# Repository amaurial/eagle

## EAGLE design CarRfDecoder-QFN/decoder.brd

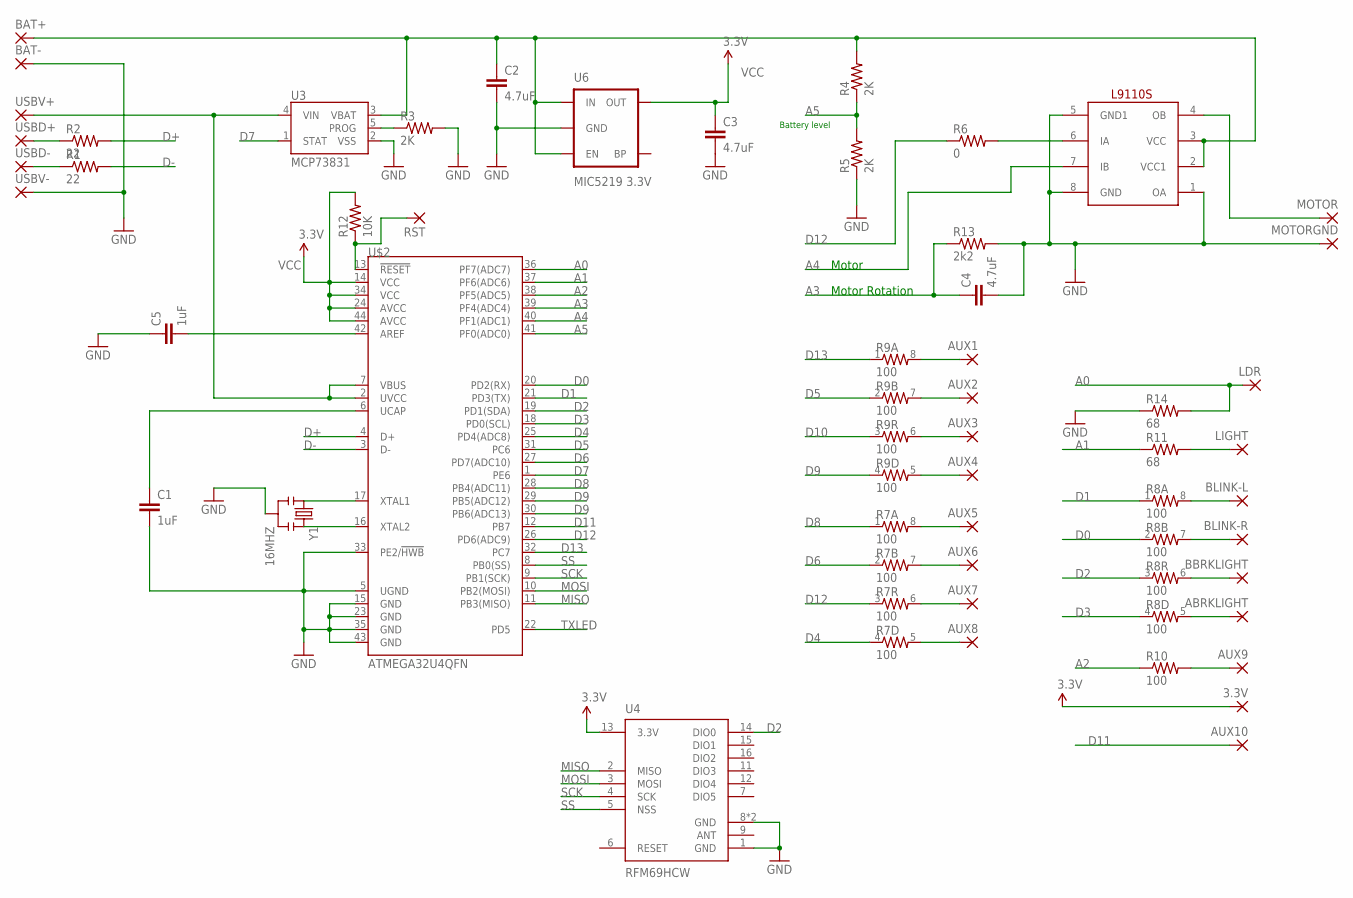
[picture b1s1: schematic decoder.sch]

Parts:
3.3V: SMD2; SMD1,27-2,54
ABRKLIGHT: SMD2; SMD1,27-2,54
AUX1, AUX2, AUX3, AUX4, AUX5, AUX6, AUX7, AUX8, AUX9, AUX10: SMD2; SMD1,27-2,54
BAT+: SMD2; SMD1,27-2,54
BAT-: SMD2; SMD1,27-2,54
BBRKLIGHT: SMD2; SMD1,27-2,54
BLINK-L: SMD2; SMD1,27-2,54
BLINK-R: SMD2; SMD1,27-2,54
C1, C5: 1uF; 0805
C2, C3, C4: 4.7uF; 0805
LDR: SMD2; SMD1,27-2,54
LIGHT: SMD2; SMD1,27-2,54
MOTOR: SMD2; SMD1,27-2,54
MOTORGND: SMD2; SMD1,27-2,54
R1, R2: 22; 0603-RES
R3, R4, R5: 2K; 0603-RES
R6: 0; 0603-RES
R7, R8, R9: 100; 0603-ARV
R10: 100; 0603-RES
R11, R14: 68; 0603-RES
R12: 10K; 0603-RES
R13: 2k2; 0603-RES
RST: SMD2; SMD1,27-2,54
U3: MCP73831; SOT23-5
U4: RFM69HCW; RFM69HCW-XXXS2
U6: MIC5219 3.3V; SOT23-5
U$1: L9110S; SO08
U$2: ATMEGA32U4QFN; SPARKFUN-DIGITALIC_QFN-44
USBD+: SMD2; SMD1,27-2,54
USBD-: SMD2; SMD1,27-2,54
USBV+: SMD2; SMD1,27-2,54
USBV-: SMD2; SMD1,27-2,54
Y1: 16MHZ; RESONATOR-SMD

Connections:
A0: LDR.1, R14.2, U$2.36 (PF7(ADC7))
A1: R11.1, U$2.37 (PF6(ADC6))
A2: R10.1, U$2.38 (PF5(ADC5))
A3: C4.1, R13.1, U$2.39 (PF4(ADC4))
A4: U$1.7 (IB), U$2.40 (PF1(ADC1))
A5: R4.1, R5.2, U$2.41 (PF0(ADC0))
D0: R8.2 (1), U$2.20 (PD2(RX))
D1: R8.1, U$2.21 (PD3(TX))
D2: R8.3 (1), U4.14 (DIO0), U$2.19 (PD1(SDA))
D3: R8.4 (1), U$2.18 (PD0(SCL))
D4: R7.4 (1), U$2.25 (PD4(ADC8))
D5: R9.2 (1), U$2.31 (PC6)
D6: R7.2 (1), U$2.27 (PD7(ADC10))
D7: U3.1 (STAT), U$2.1 (PE6)
D8: R7.1, U$2.28 (PB4(ADC11))
D9: R9.4 (1), U$2.29 (PB5(ADC12))
D10: R9.3 (1), U$2.30 (PB6(ADC13))
D11: AUX10.1, U$2.12 (PB7)
D12: R6.1, R7.3 (1), U$2.26 (PD6(ADC9))
D13: R9.1, U$2.32 (PC7)
D+: R2.2, U$2.4 (D+)
D-: R1.2, U$2.3 (D-)
GND: BAT-.1, C1.2, C2.2, C3.2, C4.2, C5.1, MOTORGND.1, R3.2, R5.1, R13.2, R14.1, U3.2 (VSS), U4.1 (GND), U4.8 (GND), U4.10 (GND), U6.2 (GND), U$1.1 (OA), U$1.5 (GND1), U$1.8 (GND), U$2.5 (UGND), U$2.15 (GND), U$2.23 (GND), U$2.33 (PE2/!HWB), U$2.35 (GND), U$2.43 (GND), USBV-.1, Y1.2
MISO: U4.2 (MISO), U$2.11 (PB3(MISO))
MOSI: U4.3 (MOSI), U$2.10 (PB2(MOSI))
unnamed: C1.1, U$2.6 (UCAP)
unnamed: C5.2, U$2.42 (AREF)
unnamed: U$2.17 (XTAL1), Y1.1
unnamed: U$2.16 (XTAL2), Y1.3
unnamed: R12.1, RST.1, U$2.13 (!RESET)
unnamed: R2.1, USBD+.1
unnamed: R1.1, USBD-.1
unnamed: U3.4 (VIN), U$2.2 (UVCC), U$2.7 (VBUS), USBV+.1
unnamed: BAT+.1, C2.1, R4.2, U3.3 (VBAT), U6.1 (IN), U6.3 (EN), U$1.2 (VCC1), U$1.3 (VCC)
unnamed: R3.1, U3.5 (PROG)
unnamed: LIGHT.1, R11.2
unnamed: BLINK-L.1, R8.8 (2)
unnamed: R6.2, U$1.6 (IA)
unnamed: BLINK-R.1, R8.7 (2)
unnamed: BBRKLIGHT.1, R8.6 (2)
unnamed: ABRKLIGHT.1, R8.5 (2)
unnamed: AUX1.1, R9.8 (2)
unnamed: AUX2.1, R9.7 (2)
unnamed: AUX3.1, R9.6 (2)
unnamed: AUX4.1, R9.5 (2)
unnamed: AUX5.1, R7.8 (2)
unnamed: AUX6.1, R7.7 (2)
unnamed: AUX7.1, R7.6 (2)
unnamed: AUX8.1, R7.5 (2)
unnamed: AUX9.1, R10.2
OB: MOTOR.1, U$1.4 (OB)
SCK: U4.4 (SCK), U$2.9 (PB1(SCK))
SS: U4.5 (NSS), U$2.8 (PB0(SS))
TXLED: U$2.22 (PD5)
VCC: 3.3V.1, C3.1, R12.2, U4.13 (3.3V), U6.5 (OUT), U$2.14 (VCC), U$2.24 (AVCC), U$2.34 (VCC), U$2.44 (AVCC)

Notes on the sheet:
Battery level
Motor
Motor Rotation

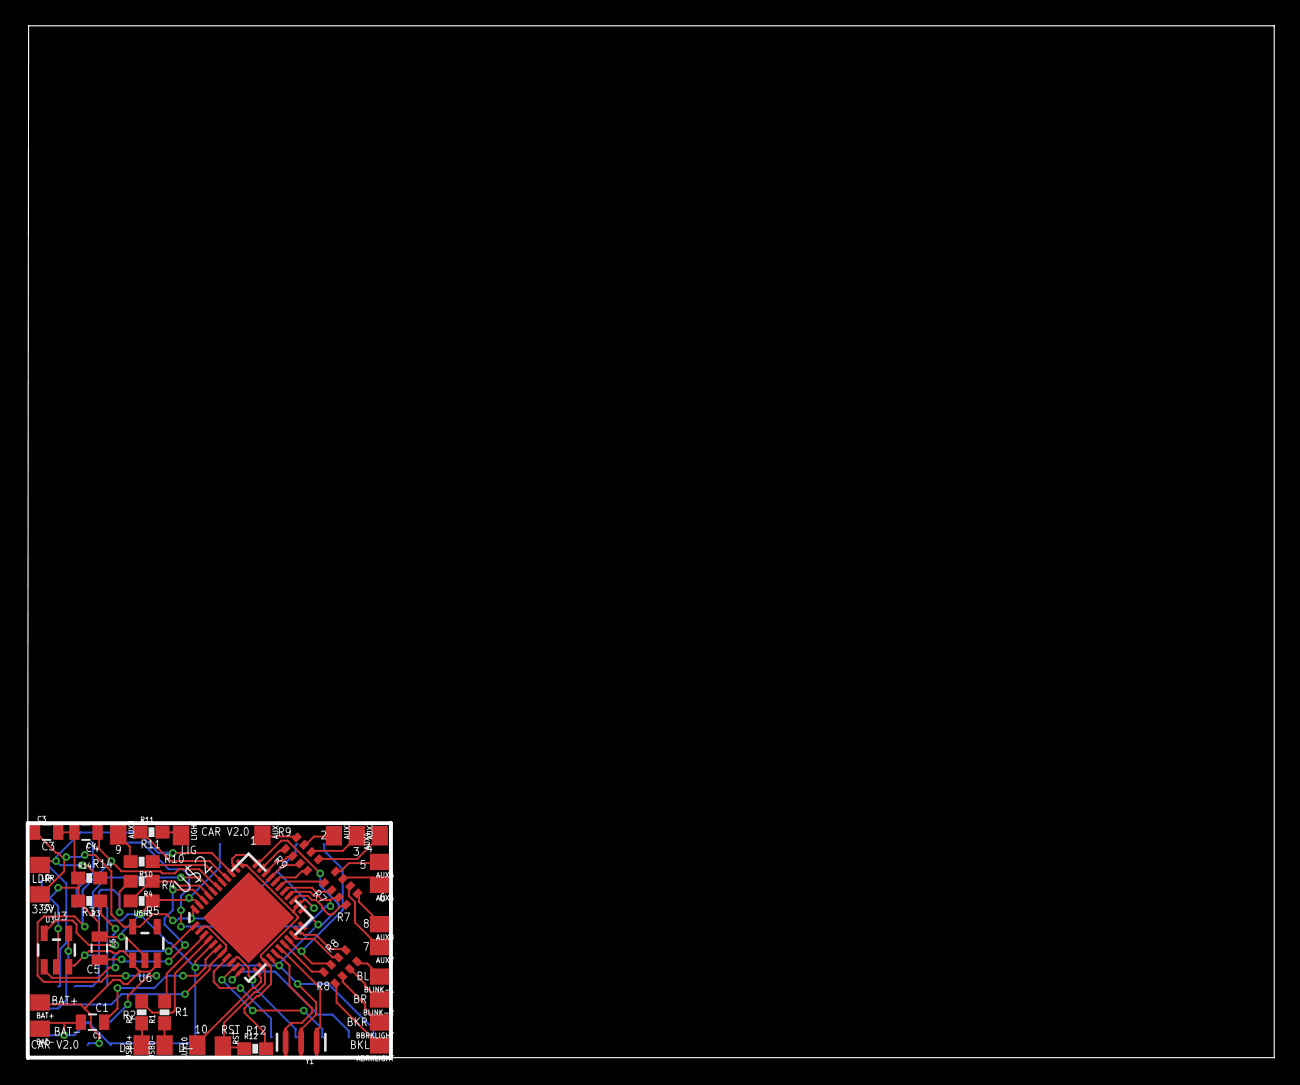
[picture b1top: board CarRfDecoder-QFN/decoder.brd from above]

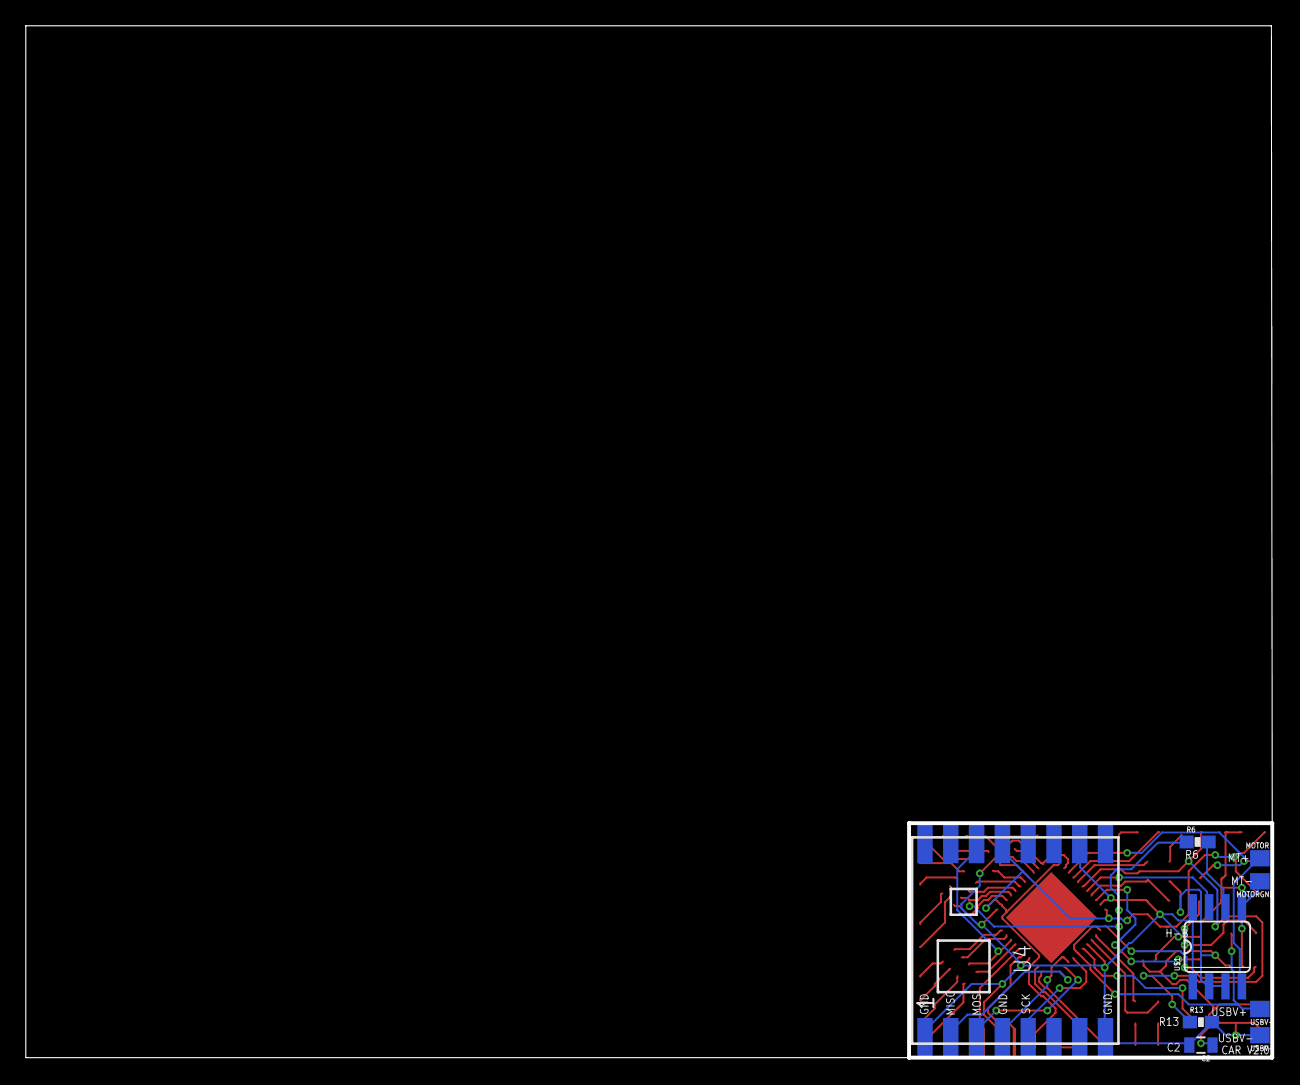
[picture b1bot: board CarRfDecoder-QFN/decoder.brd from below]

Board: 2 copper layers, 96.6 x 80.0 mm, 51 parts (9 on the bottom side), 54 nets.

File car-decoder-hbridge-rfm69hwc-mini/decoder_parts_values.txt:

Partlist exported from /home/user/amauriala/eagle/CarRfDecoder/decoder.sch at 19/08/15 9:59 AM

Qty Value             Device                 Package       Parts                                                                                                                                                                                             Description                                                                             PROD_ID    VALUE       
1                     DIODESOD-523           SOD-523       D1                                                                                                                                                                                                Diode                                                                                                          
26                    SMD2                   SMD1,27-2,54  2.56V, 3.3V, AUX-BREAKLIGHT, AUX1, AUX2, AUX3, AUX4, AUX5, AUX6, AUX7, AUX8, AUX9, AUX10, BACK-BREAKLIGHT, BLINK-L, BLINK-R, GND, LDR, LIGHT, MOTOR, MOTORGND, USBD+, USBD-, USBV+, USBV+2, USBV- SMD PAD                                                                                                        
3   100               RESISTOR-ARRAY0603-ARV 0603-ARV      R7, R8, R9                                                                                                                                                                                        Array Chip Resistor                                                                                            
1   100               RESISTOR0603-RES       0603-RES      R10                                                                                                                                                                                               Resistor                                                                                                       
1   1uF               CAP0805                0805          C1                                                                                                                                                                                                Capacitor                                                                                                      
2   22                RESISTOR0603-RES       0603-RES      R1, R2                                                                                                                                                                                            Resistor                                                                                                       
3   2K                RESISTOR0603-RES       0603-RES      R3, R4, R5                                                                                                                                                                                        Resistor                                                                                                       
1   2k2               RESISTOR-ARRAY0603-ARV 0603-ARV      R6                                                                                                                                                                                                Array Chip Resistor                                                                                            
3   4.7uF             CAP0805                0805          C2, C3, C4                                                                                                                                                                                        Capacitor                                                                                                      
2   68                RESISTOR0603-RES       0603-RES      10K, R11                                                                                                                                                                                          Resistor                                                                                                       
1   ATMEGA32U4TQFP-44 ATMEGA32U4TQFP-44      TQFP44        U1                                                                                                                                                                                                Atmel 44-pin 8-bit Microcontroller with 32KBytes of ISP Flash and USB Controller                               
2   BC847             BC847                  SOT23         T1, T2                                                                                                                                                                                            NPN TRANSISTOR                                                                                                 
1   IRLML6402         MOSFET-P-SOT23         SOT23         T3                                                                                                                                                                                                P-Channel MOSFET (e.g.  IRLML6402)                                                                             
1   MCP73831          MCP73831               SOT23-5       U3                                                                                                                                                                                                Miniature single cell, fully integrated Li-Ion, Li-polymer charge management controller IC-09995               
1   MIC5219 3.3V      V_REG_MIC52193.3V      SOT23-5       U6                                                                                                                                                                                                V_REG MIC5219                                                                           VREG-09872 MIC5219 3.3V
1   RFM69CW           RFM69CW                RFM69CW-XXXS2 U2

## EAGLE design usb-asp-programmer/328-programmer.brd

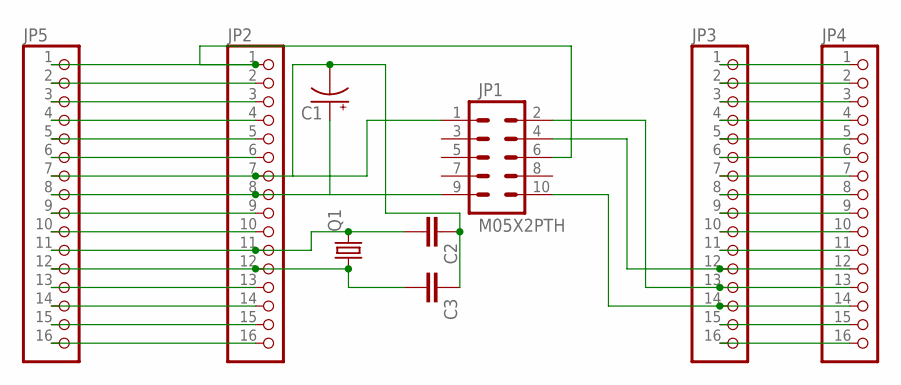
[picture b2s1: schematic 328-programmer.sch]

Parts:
C1: CPOL-USE2.5-7; E2,5-7
C2, C3: CAPPTH2; CAP-PTH-SMALL2
JP1: M05X2PTH; AVR_ICSP
JP2, JP3, JP4, JP5: PINHD-1X16; 1X16
Q1: CRYSTALHC49S; HC49/S

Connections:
CR1: C3.2, JP2.12, JP5.12, Q1.1
CR2: C2.2, JP2.11, JP5.11, Q1.2
GND: C1.-, C2.1, C3.1, JP1.1, JP2.7, JP5.7
unnamed: JP3.16, JP4.16
unnamed: JP3.15, JP4.15
unnamed: JP3.11, JP4.11
unnamed: JP3.10, JP4.10
unnamed: JP3.9, JP4.9
unnamed: JP3.8, JP4.8
unnamed: JP3.7, JP4.7
unnamed: JP3.6, JP4.6
unnamed: JP3.5, JP4.5
unnamed: JP3.4, JP4.4
unnamed: JP3.3, JP4.3
unnamed: JP3.2, JP4.2
unnamed: JP3.1, JP4.1
unnamed: JP2.16, JP5.16
unnamed: JP2.15, JP5.15
unnamed: JP2.14, JP5.14
unnamed: JP2.13, JP5.13
unnamed: JP2.10, JP5.10
unnamed: JP2.9, JP5.9
unnamed: JP2.6, JP5.6
unnamed: JP2.5, JP5.5
unnamed: JP2.4, JP5.4
unnamed: JP2.3, JP5.3
unnamed: JP2.2, JP5.2
RST: JP1.6, JP2.1, JP5.1
SCK: JP1.4, JP3.12, JP4.12
SI: JP1.10, JP3.14, JP4.14
SO: JP1.2, JP3.13, JP4.13
VCC: C1.+, JP1.9, JP2.8, JP5.8

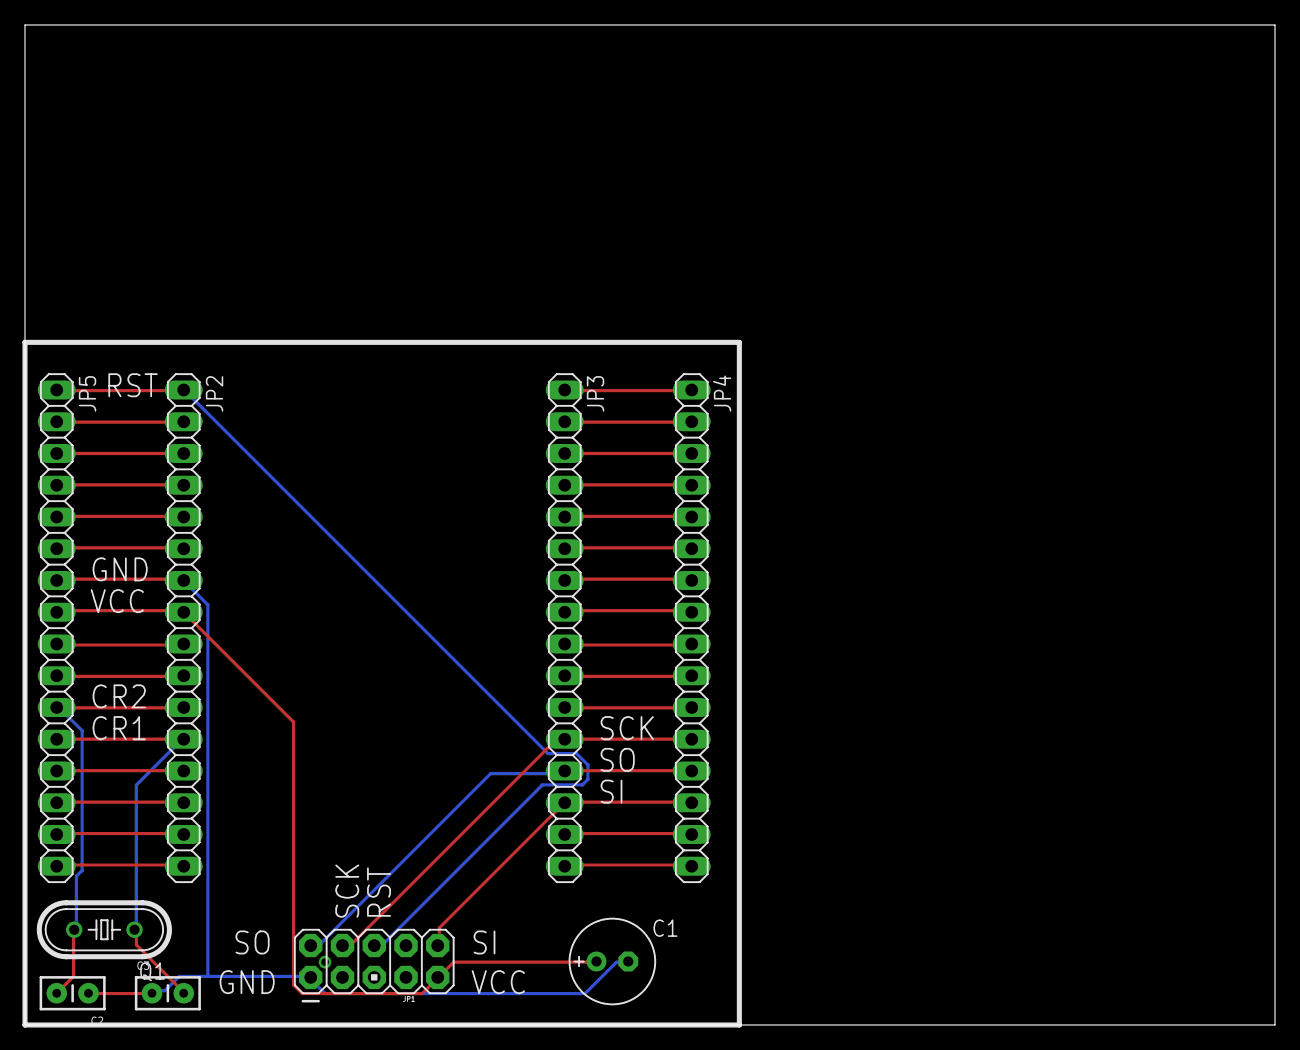
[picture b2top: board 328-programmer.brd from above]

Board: 2 copper layers, 100.0 x 80.0 mm, 9 parts (0 on the bottom side), 32 nets.

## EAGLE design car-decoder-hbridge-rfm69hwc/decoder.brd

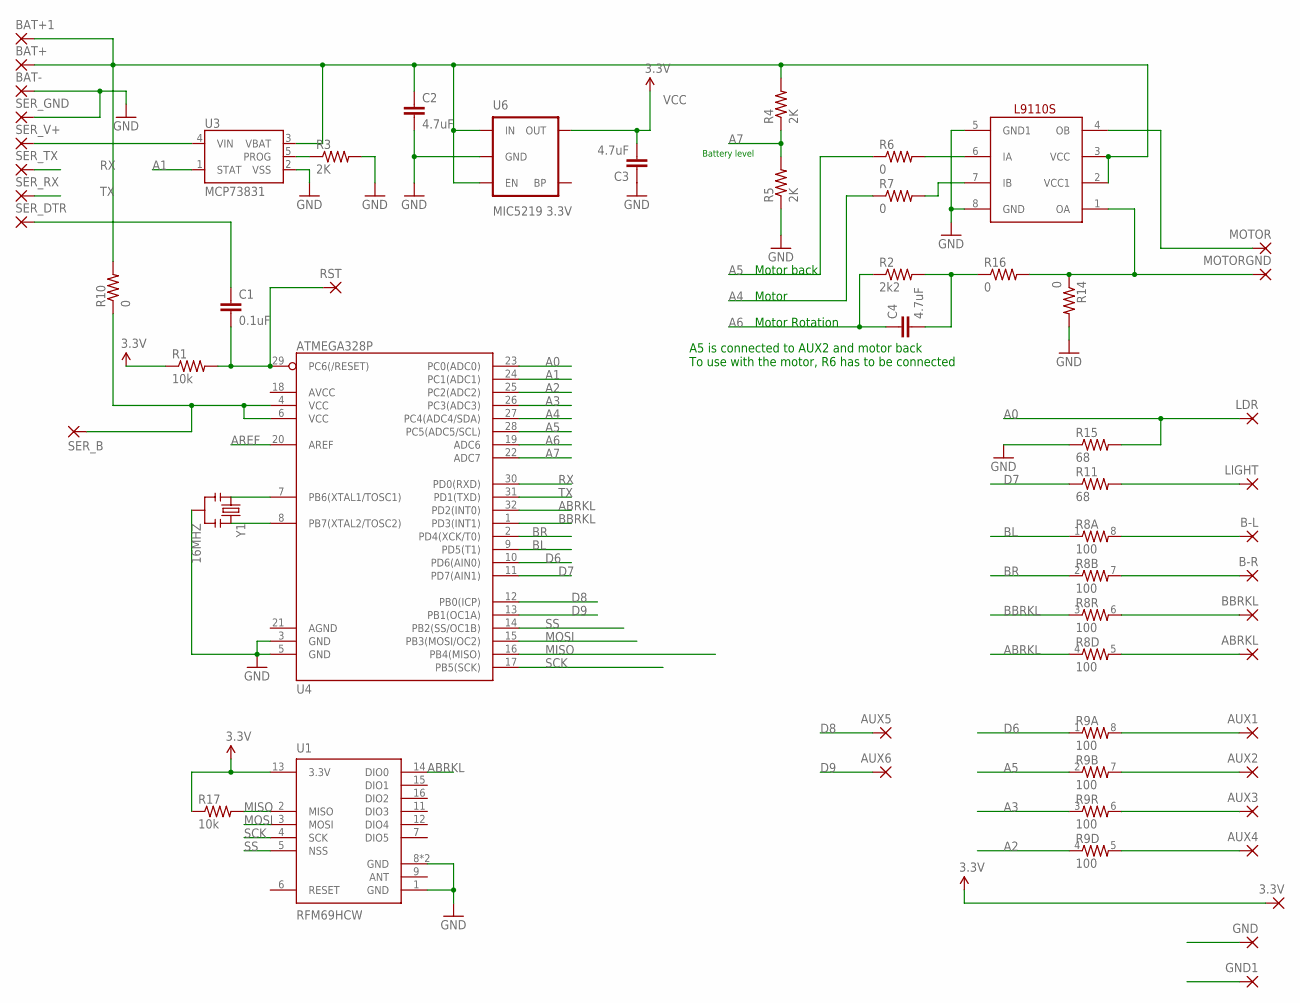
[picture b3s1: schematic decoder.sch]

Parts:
3.3V: SMD2; SMD1,27-2,54
ABRKL: SMD2; SMD1,27-2,54
AUX1, AUX2, AUX3, AUX4, AUX5, AUX6: SMD2; SMD1,27-2,54
B-L: SMD2; SMD1,27-2,54
B-R: SMD2; SMD1,27-2,54
BAT+, BAT+1: SMD2; SMD1,27-2,54
BAT-: SMD2; SMD1,27-2,54
BBRKL: SMD2; SMD1,27-2,54
C1: 0.1uF; 0805
C2, C3, C4: 4.7uF; 0805
GND, GND1: SMD2; SMD1,27-2,54
LDR: SMD2; SMD1,27-2,54
LIGHT: SMD2; SMD1,27-2,54
MDRIVER: L9110S; SO08
MOTOR: SMD2; SMD1,27-2,54
MOTORGND: SMD2; SMD1,27-2,54
R1, R17: 10k; 0603-RES
R2: 2k2; 0603-RES
R3, R4, R5: 2K; 0603-RES
R6, R7, R10, R14, R16: 0; 0603-RES
R8, R9: 100; 0603-ARV
R11, R15: 68; 0603-RES
RST: SMD2; SMD1,27-2,54
SER_B: SMD2; SMD1,27-2,54
SER_DTR: SMD2; SMD1,27-2,54
SER_GND: SMD2; SMD1,27-2,54
SER_RX: SMD2; SMD1,27-2,54
SER_TX: SMD2; SMD1,27-2,54
SER_V+: SMD2; SMD1,27-2,54
U1: RFM69HCW; RFM69HCW-XXXS2
U3: MCP73831; SOT23-5
U4: ATMEGA328P; TQFP32-08
U6: MIC5219 3.3V; SOT23-5
Y1: 16MHZ; RESONATOR-SMD

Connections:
A0: LDR.1, R15.2, U4.23 (PC0(ADC0))
A1: U3.1 (STAT), U4.24 (PC1(ADC1))
A2: R9.4 (1), U4.25 (PC2(ADC2))
A3: R9.3 (1), U4.26 (PC3(ADC3))
A4: R7.1, U4.27 (PC4(ADC4/SDA))
A5: R6.1, R9.2 (1), U4.28 (PC5(ADC5/SCL))
A6: C4.1, R2.1, U4.19 (ADC6)
A7: R4.1, R5.2, U4.22 (ADC7)
ABRKL: R8.4 (1), U1.14 (DIO0), U4.32 (PD2(INT0))
AREF: U4.20 (AREF)
BAT+: BAT+.1, BAT+1.1, C2.1, MDRIVER.2 (VCC1), MDRIVER.3 (VCC), R4.2, R10.2, U3.3 (VBAT), U6.1 (IN), U6.3 (EN)
BBRKL: R8.3 (1), U4.1 (PD3(INT1))
BL: R8.1, U4.9 (PD5(T1))
BR: R8.2 (1), U4.2 (PD4(XCK/T0))
D6: R9.1, U4.10 (PD6(AIN0))
D7: R11.1, U4.11 (PD7(AIN1))
D8: AUX5.1, U4.12 (PB0(ICP))
D9: AUX6.1, U4.13 (PB1(OC1A))
GND: BAT-.1, C2.2, C3.1, GND.1, GND1.1, MDRIVER.5 (GND1), MDRIVER.8 (GND), R3.2, R5.1, R14.2, R15.1, SER_GND.1, U1.1 (GND), U1.8 (GND), U1.10 (GND), U3.2 (VSS), U4.3 (GND), U4.5 (GND), U6.2 (GND), Y1.2
MISO: R17.2, U1.2 (MISO), U4.16 (PB4(MISO))
MOSI: U1.3 (MOSI), U4.15 (PB3(MOSI/OC2))
unnamed: C4.2, R2.2, R16.1
unnamed: U4.7 (PB6(XTAL1/TOSC1)), Y1.1
unnamed: C1.1, SER_DTR.1
unnamed: U4.8 (PB7(XTAL2/TOSC2)), Y1.3
unnamed: C1.2, R1.2, RST.1, U4.29 (PC6(/RESET))
unnamed: MDRIVER.6 (IA), R6.2
unnamed: MDRIVER.7 (IB), R7.2
unnamed: R10.1, SER_B.1, U4.4 (VCC), U4.6 (VCC)
unnamed: SER_V+.1, U3.4 (VIN)
unnamed: R3.1, U3.5 (PROG)
unnamed: LIGHT.1, R11.2
unnamed: B-L.1, R8.8 (2)
unnamed: B-R.1, R8.7 (2)
unnamed: BBRKL.1, R8.6 (2)
unnamed: ABRKL.1, R8.5 (2)
unnamed: AUX1.1, R9.8 (2)
unnamed: AUX2.1, R9.7 (2)
unnamed: AUX3.1, R9.6 (2)
unnamed: AUX4.1, R9.5 (2)
OA: MDRIVER.1 (OA), MOTORGND.1, R14.1, R16.2
OB: MDRIVER.4 (OB), MOTOR.1
RX: SER_TX.1, U4.30 (PD0(RXD))
SCK: U1.4 (SCK), U4.17 (PB5(SCK))
SS: U1.5 (NSS), U4.14 (PB2(SS/OC1B))
TX: SER_RX.1, U4.31 (PD1(TXD))
VCC: 3.3V.1, C3.2, R1.1, R17.1, U1.13 (3.3V), U6.5 (OUT)

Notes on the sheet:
Battery level
Motor
Motor Rotation
Motor back
A5 is connected to AUX2 and motor back To use with the motor, R6 has to be connected

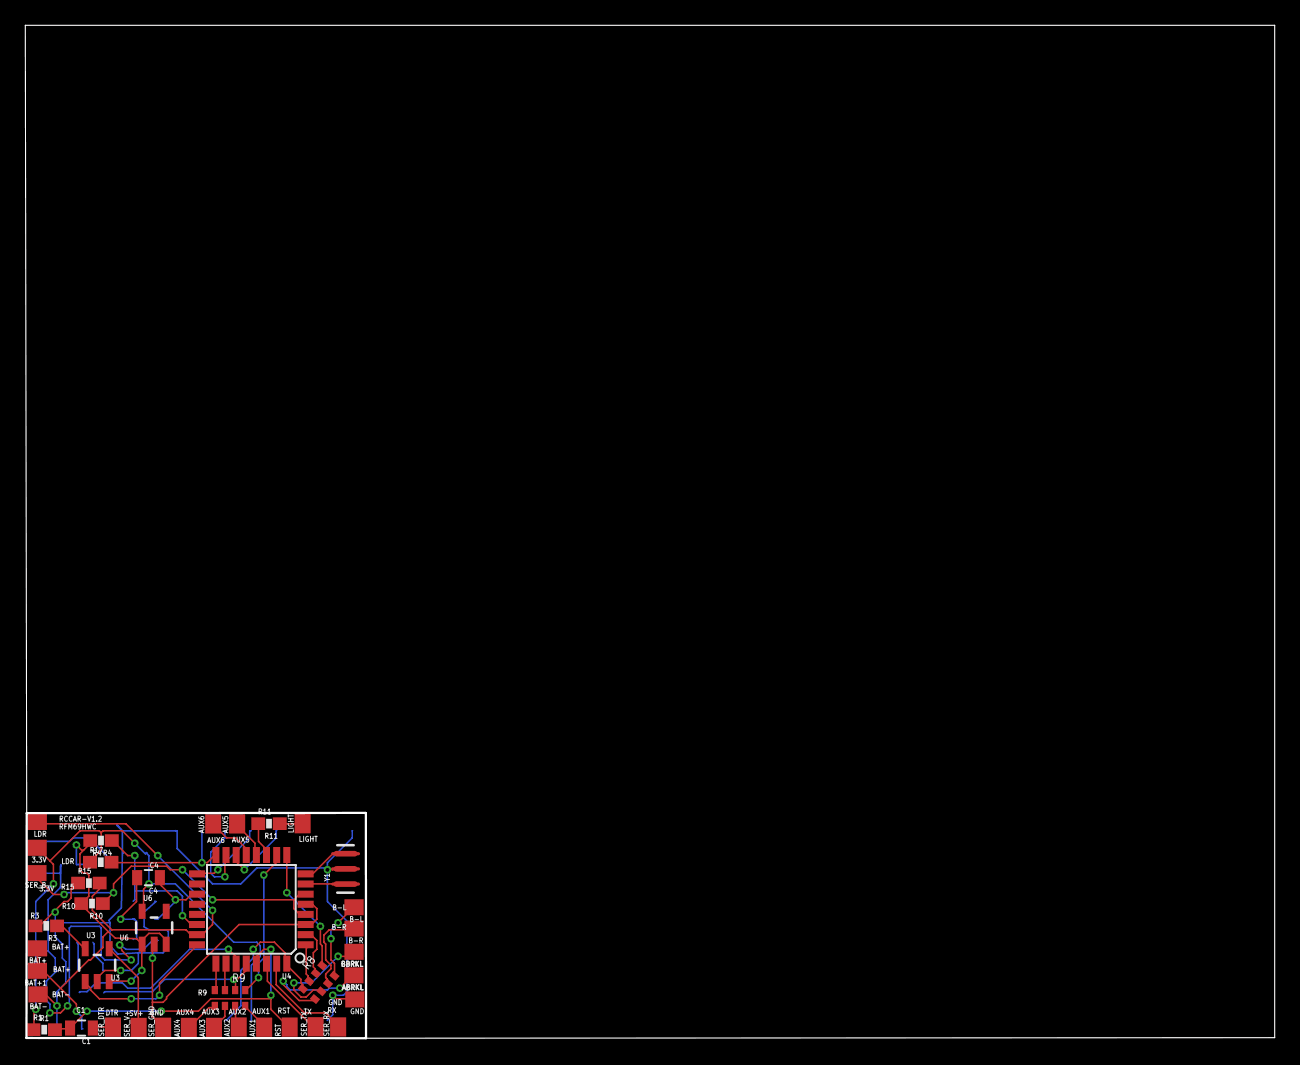
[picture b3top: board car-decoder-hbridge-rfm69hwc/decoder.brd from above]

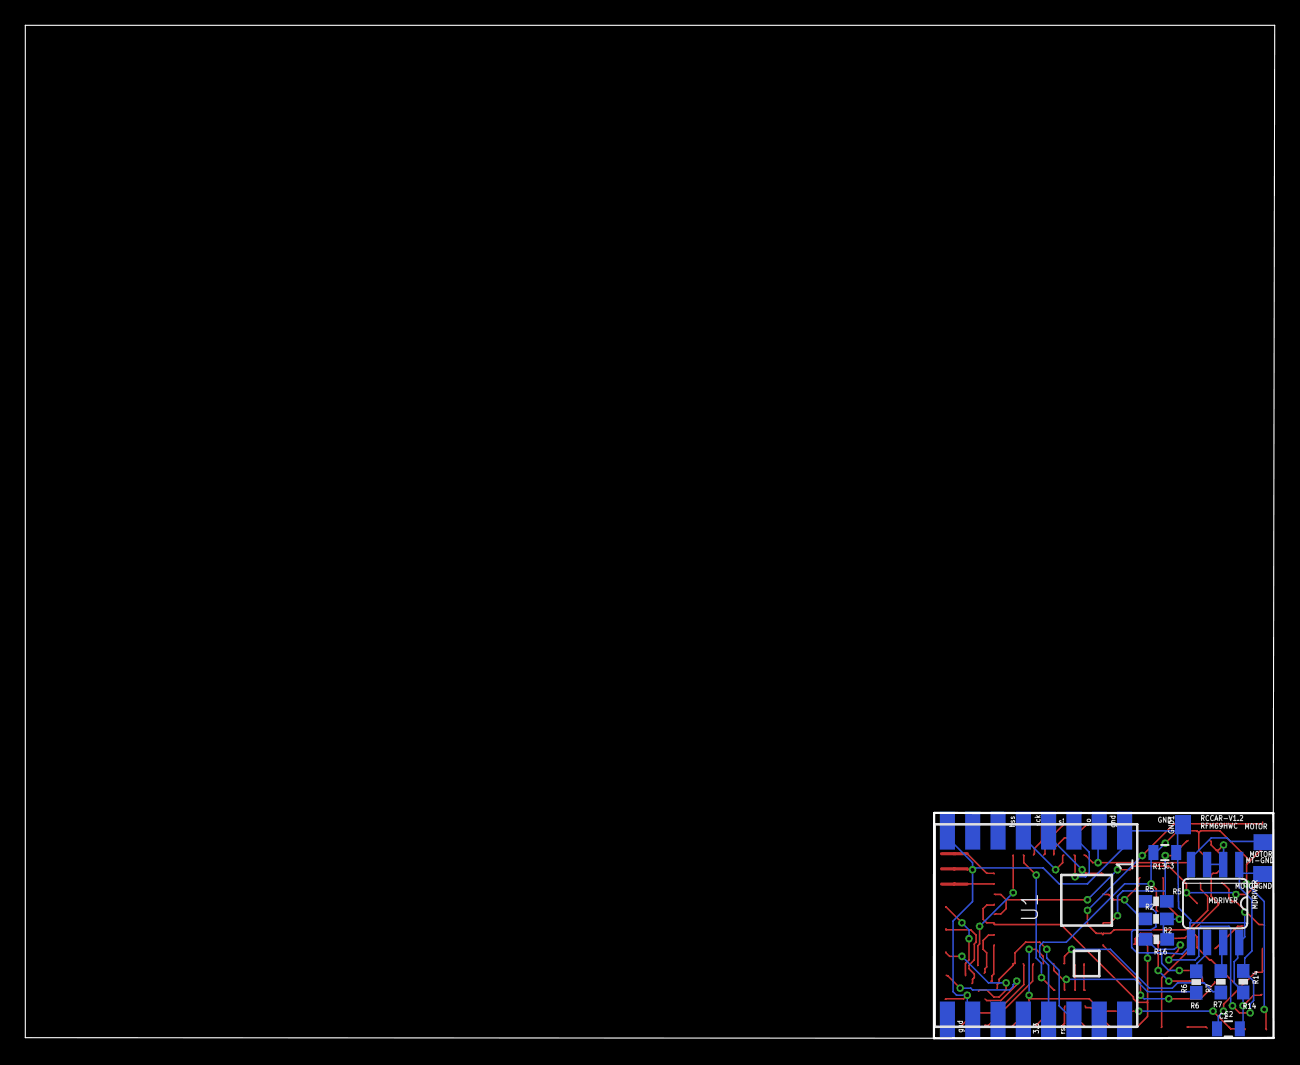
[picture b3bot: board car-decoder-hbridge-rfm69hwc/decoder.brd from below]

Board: 2 copper layers, 98.7 x 80.0 mm, 52 parts (13 on the bottom side), 46 nets.

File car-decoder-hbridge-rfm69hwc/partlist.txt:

Partlist

Exported from decoder.sch at 2/08/19 12:12 PM

EAGLE Version 7.2.0 Copyright (c) 1988-2014 CadSoft

Assembly variant: 

Part     Value          Device                 Package        Library             Sheet

3.3V                    SMD2                   SMD1,27-2,54   wirepad             1
ABRKL                   SMD2                   SMD1,27-2,54   wirepad             1
AUX1                    SMD2                   SMD1,27-2,54   wirepad             1
AUX2                    SMD2                   SMD1,27-2,54   wirepad             1
AUX3                    SMD2                   SMD1,27-2,54   wirepad             1
AUX4                    SMD2                   SMD1,27-2,54   wirepad             1
B-L                     SMD2                   SMD1,27-2,54   wirepad             1
B-R                     SMD2                   SMD1,27-2,54   wirepad             1
BAT+                    SMD2                   SMD1,27-2,54   wirepad             1
BAT+1                   SMD2                   SMD1,27-2,54   wirepad             1
BAT-                    SMD2                   SMD1,27-2,54   wirepad             1
BBRKL                   SMD2                   SMD1,27-2,54   wirepad             1
C1       0.1uF          CAP0805                0805           SparkFun-Capacitors 1
C2       4.7uF          CAP0805                0805           SparkFun-Capacitors 1
C3       4.7uF          CAP0805                0805           SparkFun-Capacitors 1
C4       4.7uF          CAP0805                0805           SparkFun-Capacitors 1
GND                     SMD2                   SMD1,27-2,54   wirepad             1
GND1                    SMD2                   SMD1,27-2,54   wirepad             1
LDR                     SMD2                   SMD1,27-2,54   wirepad             1
LIGHT                   SMD2                   SMD1,27-2,54   wirepad             1
MDRIVER  L9110S         L9110S                 SO08           h-bridge-l9119s     1
MOTOR                   SMD2                   SMD1,27-2,54   wirepad             1
MOTORGND                SMD2                   SMD1,27-2,54   wirepad             1
R1       10k            RESISTOR0603-RES       0603-RES       SparkFun-Resistors  1
R2       2k2            RESISTOR0603-RES       0603-RES       SparkFun-Resistors  1
R3       2K             RESISTOR0603-RES       0603-RES       SparkFun-Resistors  1
R4       2K             RESISTOR0603-RES       0603-RES       SparkFun-Resistors  1
R5       2K             RESISTOR0603-RES       0603-RES       SparkFun-Resistors  1
R6       0              RESISTOR0603-RES       0603-RES       SparkFun-Resistors  1
R7       0              RESISTOR0603-RES       0603-RES       SparkFun-Resistors  1
R8       100            RESISTOR-ARRAY0603-ARV 0603-ARV       SparkFun-Resistors  1
R9       100            RESISTOR-ARRAY0603-ARV 0603-ARV       SparkFun-Resistors  1
R10      0              RESISTOR0603-RES       0603-RES       SparkFun-Resistors  1
R11      68             RESISTOR0603-RES       0603-RES       SparkFun-Resistors  1
R14      0              RESISTOR0603-RES       0603-RES       SparkFun-Resistors  1
R15      68             RESISTOR0603-RES       0603-RES       SparkFun-Resistors  1
R16      0              RESISTOR0603-RES       0603-RES       SparkFun-Resistors  1
R17      10k            RESISTOR0603-RES       0603-RES       SparkFun-Resistors  1
RST                     SMD2                   SMD1,27-2,54   wirepad             1
SER_B                   SMD2                   SMD1,27-2,54   wirepad             1
SER_DTR                 SMD2                   SMD1,27-2,54   wirepad             1
SER_GND                 SMD2                   SMD1,27-2,54   wirepad             1
SER_RX                  SMD2                   SMD1,27-2,54   wirepad             1
SER_TX                  SMD2                   SMD1,27-2,54   wirepad             1
SER_V+                  SMD2                   SMD1,27-2,54   wirepad             1
U1       RFM69HCW       RFM69HCW               RFM69HCW-XXXS2 SparkFun-RF         1
U3       MCP73831       MCP73831               SOT23-5        SparkFun-PowerIC    1
U4       ATMEGA328P     ATMEGA328_SMT          TQFP32-08      SparkFun-DigitalIC  1
U6       MIC5219 3.3V   V_REG_MIC52193.3V      SOT23-5        SparkFun-PowerIC    1
Y1       16MHZ          RESONATOR16MHZ         RESONATOR-SMD  SparkFun-FreqCtrl   1

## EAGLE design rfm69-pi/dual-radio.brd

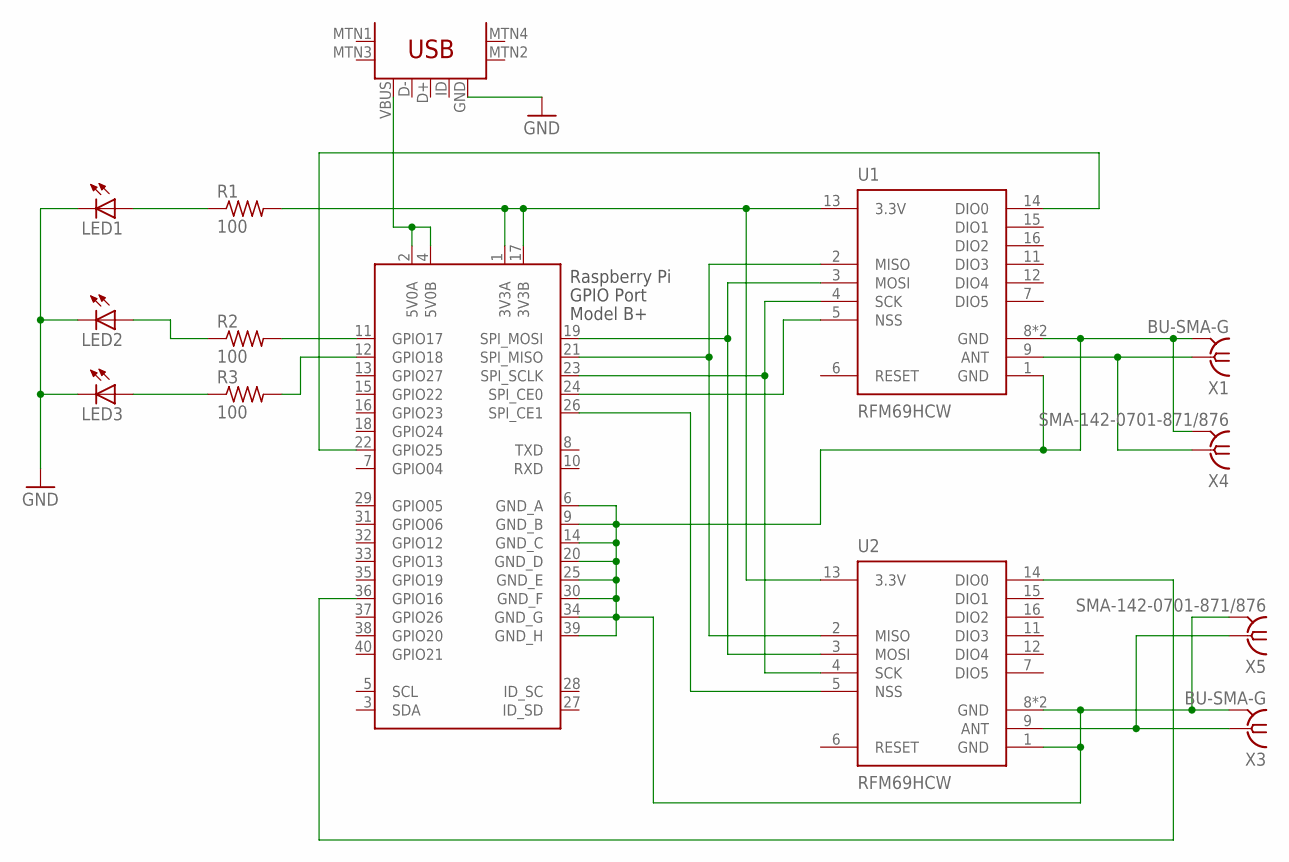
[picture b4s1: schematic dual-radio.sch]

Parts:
LED1, LED2, LED3: LEDSML0805; SML0805
R1, R2, R3: 100; M0805
U1, U2: RFM69HCW; RFM69HCW-XXXS2
U$1: USB-MINIB-5PIN; USB-MINIB
X1, X3: BU-SMA-G
X2: RASPI_BOARD_B+#_HDC; RASPI_BOARD_B+HAT_DF_CF
X4, X5: SMA-142-0701-871/876; J502-ND-142-0701-871/876

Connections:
GND: LED1.C, LED2.C, LED3.C, U$1.GND
unnamed: R1.2, U1.13 (3.3V), U2.13 (3.3V), X2.1 (3V3A), X2.17 (3V3B)
unnamed: U1.2 (MISO), U2.2 (MISO), X2.21 (SPI_MISO)
unnamed: U1.3 (MOSI), U2.3 (MOSI), X2.19 (SPI_MOSI)
unnamed: U1.4 (SCK), U2.4 (SCK), X2.23 (SPI_SCLK)
unnamed: U1.5 (NSS), X2.24 (SPI_CE0)
unnamed: U2.5 (NSS), X2.26 (SPI_CE1)
unnamed: U1.1 (GND), U1.8 (GND), U1.10 (GND), U2.1 (GND), U2.8 (GND), U2.10 (GND), X1.2, X1.3 (2), X1.4 (2), X1.5 (2), X2.6 (GND_A), X2.9 (GND_B), X2.14 (GND_C), X2.20 (GND_D), X2.25 (GND_E), X2.30 (GND_F), X2.34 (GND_G), X2.39 (GND_H), X3.2, X3.3 (2), X3.4 (2), X3.5 (2), X4.G@1 (2), X4.G@2 (2), X4.G@3 (2), X4.G@4 (2), X5.G@1 (2), X5.G@2 (2), X5.G@3 (2), X5.G@4 (2)
unnamed: U1.14 (DIO0), X2.22 (GPIO25)
unnamed: U2.14 (DIO0), X2.36 (GPIO16)
unnamed: U1.9 (ANT), X1.1, X4.1
unnamed: U2.9 (ANT), X3.1, X5.1
unnamed: R2.2, X2.11 (GPIO17)
unnamed: R3.2, X2.12 (GPIO18)
unnamed: LED1.A, R1.1
unnamed: LED2.A, R2.1
unnamed: LED3.A, R3.1
unnamed: U$1.VBUS, X2.2 (5V0A), X2.4 (5V0B)

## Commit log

2015-01-05 Eagle projects. First commit.
2015-01-06 Wiring.
2015-01-07 Minor changes
2015-01-07 Last edit need revision
2015-01-07 Revision
2015-01-09 Crystal change
2015-01-27 Gerber files created
2015-03-01 Made correction on the main PCB. MCP2515 had wrong connections. Added some resistor and capacitors.
2015-03-01 New CAM files.
2015-03-19 Ethernet connector-previous version
2015-03-19 Board with ethernet connectors.
2015-04-01 New version.
2015-05-08 Last version with correction.
2015-05-13 imore changes
2015-07-08 CarRfDecoder first commit.
2015-07-15 more changes in carRF
2015-07-17 carsystem
2015-07-21 first version of car_decoder board
2015-07-21 lbr bkp
2015-07-26 added pin D3 to the board and changed the D11.
2015-08-05 final board decoder
2015-10-19 arduino nano lib
2015-10-19 cleaning
2015-10-19 car decoder
2015-10-19 remove proto atmega32u4
2015-11-08 cbus shield with arduino mini.
2015-11-25 car shield with atmega 328
2015-11-26 changes in the design
2015-11-29 some improvement on the boards.
2015-12-04 Ready boards.
2015-12-29 Fix connection to the rf module and add a 16mhz crystal
2015-12-30 Add gnd pad. Reduce the size
2016-01-11 Add Board with hbridge
2016-01-11 File cleaning
2016-01-16 bug fixes and better board routing
2016-01-21 Fix light board. Fix carsystem board.
2016-01-21 Remove unecessary files.
2016-01-22 CAM file for boards.
2016-01-23 Add possibility to power the board from 3.3v or direct from battery.
2016-02-03 small fixes for vcc.
2016-02-08 Better design of board
2016-05-23 Change the pin to H-bridge to allow reverse control of the motor using A5
2016-06-06 Add mux to merg Can board
2016-07-17 Fix R6 R7 bug. Disconnect motor from GND via R14
2016-10-22 add rc pcb
2016-12-02 Add a new version of the rc board, now smaller
2016-12-02 rename some projects
2016-12-04 some board simplification and isolation of motor speed sensor
2017-03-26 Add pcb project for CANPAN
2018-01-10 update the last boards
2018-12-03 New layout for RFM69HC
2019-08-01 Add rfm69 pi board and a version for the car board with small mega328
2019-08-02 Add board pictures and part lists
2019-08-21 Fix boards and add the pi control station
2019-09-20 Add labels to the usbasp for better orientation
2019-09-20 Make fixes to schematics mega32u4
2019-09-20 Add project with mega32u4 with smaller package

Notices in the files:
parts and their libraries:
SparkFun-Resistors: Licensing: Creative Commons ShareAlike 4.0 International - https://creativecommons.org/licenses/by-sa/4.0
diy-modules: Released under the Creative Commons Attribution 4.0 International License: http://creativecommons.org/licenses/by/4.0
